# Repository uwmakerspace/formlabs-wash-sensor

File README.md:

# Formlabs Wash Sensor

This repository contains the firmware and documentation for the Design Innovation Lab's Formlabs Wash Sensor. This device is designed to monitor multiple Formlabs Wash units and visually alert when a wash has completed.

The device uses a distance sensor to measure the position of the wash basket. If the sensor detects the back wall, it assumes the machines are empty or currently working. If it detects an object (the basket/print) consistently, it illuminates a WS2812B LED strip to indicate presence and position, providing visual feedback in busy environments.

## Features

- **Non-Contact Sensing:** Utilizes the VL53L0X time-of-flight distance sensor for measurement. Non-contact sensing avoids mechanical wear and resin contamination. One sensor can monitor multiple wash stations.
- **Visual Feedback:**
  - **Position Tracking:** NeoPixel strip indicates which of the wash stations needs attention based on the distance reading.
  - **Effects:** A "breathing" effect and a bi-directional pulse effect enhance visibility.
- **Noise Filtering:**
  - **Exponential Moving Average (EMA):** Heavily smooths sensor jitter
  - **Hysteresis:** "Sticky" LED positioning prevents flickering between pixels.
- **Smart Presence Detection:** Includes a 15-second delay. The LEDs will not trigger during transient events (like loading or unloading a print). The object must be detected for 15 seconds before the display activates.

## Hardware

- **Microcontroller:** ESP32-C3 "Super Mini" board
- **Sensor:** VL53L0X Time-of-Flight Distance Sensor module
- **Display:** WS2812B Addressable LED Strip

## PCB

A custom PCB was designed to integrate the components neatly and flatly against the wall. The PCB files can be found in the `kicad/` directory. It's simply mounted against the wall using double-sided tape. Nothing special about it, just better than a bunch of wires. Uses Osh Park design rules.

## Configuration

- `WALL_DISTANCE`: The distance from the sensor to the back wall. Readings beyond this turn the system off.
- `FIRST_LED_DISTANCE_OFFSET`: Distance from the sensor to the first LED on the strip.
- `SENSOR_DETECTION_OFFSET`: Compensates for the sensor detecting the front edge of an object while the LEDs should represent the center.
- `LED_SPACING`: Physical distance between LED pixels.
- `PRESENCE_TIMEOUT`: Time an object must be consistently seen before LEDs turn on.
- `FILTER_ALPHA`: Smoothing factor. Lower is smoother but slower.
- `HYSTERESIS_THRESHOLD`: How far the object must move to shift the LED pixel.

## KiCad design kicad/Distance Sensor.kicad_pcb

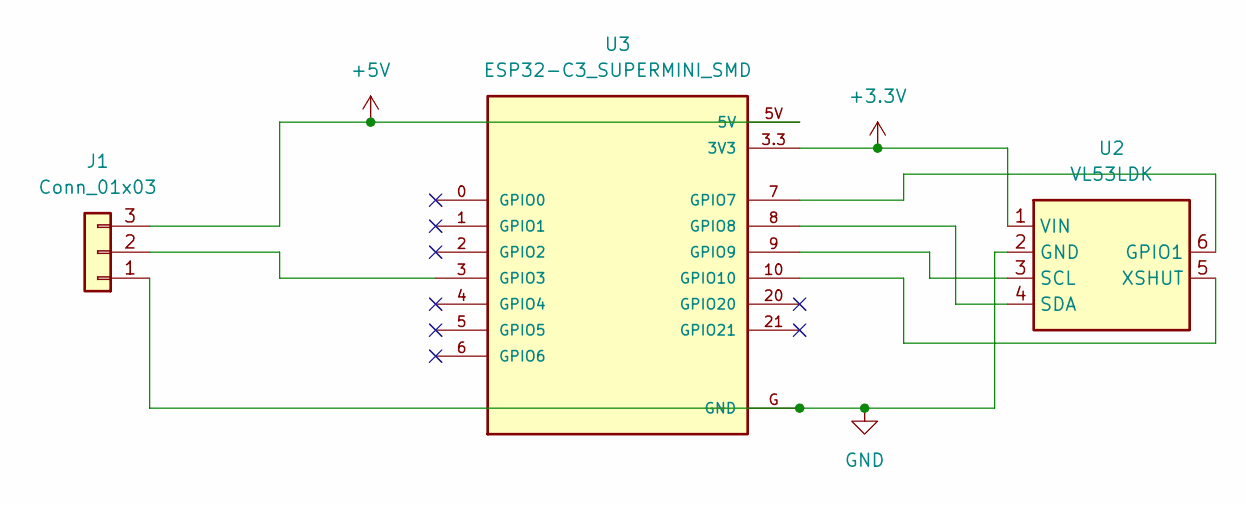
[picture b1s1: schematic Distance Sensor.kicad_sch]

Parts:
J1: Conn_01x03; PinHeader_1x03_P2.54mm_Vertical
U2: VL53LDK
U3: ESP32-C3_SUPERMINI_SMD; MODULE_ESP32-C3_SUPERMINI

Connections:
+3.3V: U2.1 (VIN), U3.3.3 (3V3)
+5V: J1.3, U3.5V
GND: J1.1, U2.2 (GND), U3.G (GND)
unnamed: J1.2, U3.3 (GPIO3)
unnamed: U2.6 (GPIO1), U3.7 (GPIO7)
unnamed: U2.3 (SCL), U3.9 (GPIO9)
unnamed: U2.4 (SDA), U3.8 (GPIO8)
unnamed: U2.5 (XSHUT), U3.10 (GPIO10)

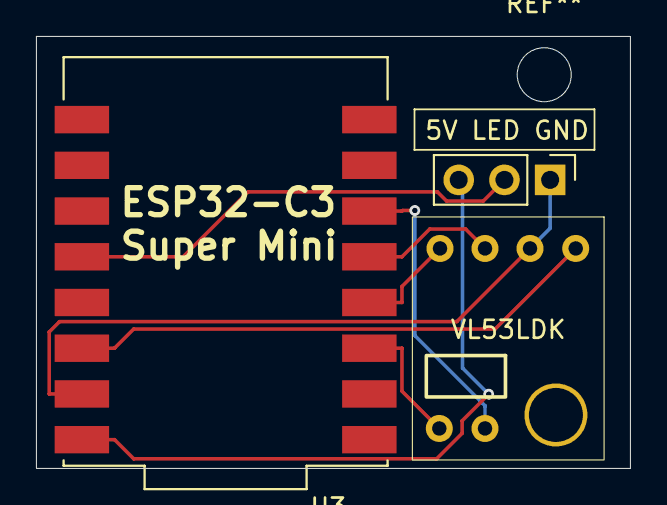
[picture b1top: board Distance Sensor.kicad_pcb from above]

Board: 2 copper layers, 33.0 x 24.0 mm, 4 parts (1 on the bottom side), 8 nets.

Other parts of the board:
kibuzzard-68CD61BF: G***; kibuzzard-68CD61BF

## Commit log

2025-11-21 Release
2025-11-29 Improve footprints
